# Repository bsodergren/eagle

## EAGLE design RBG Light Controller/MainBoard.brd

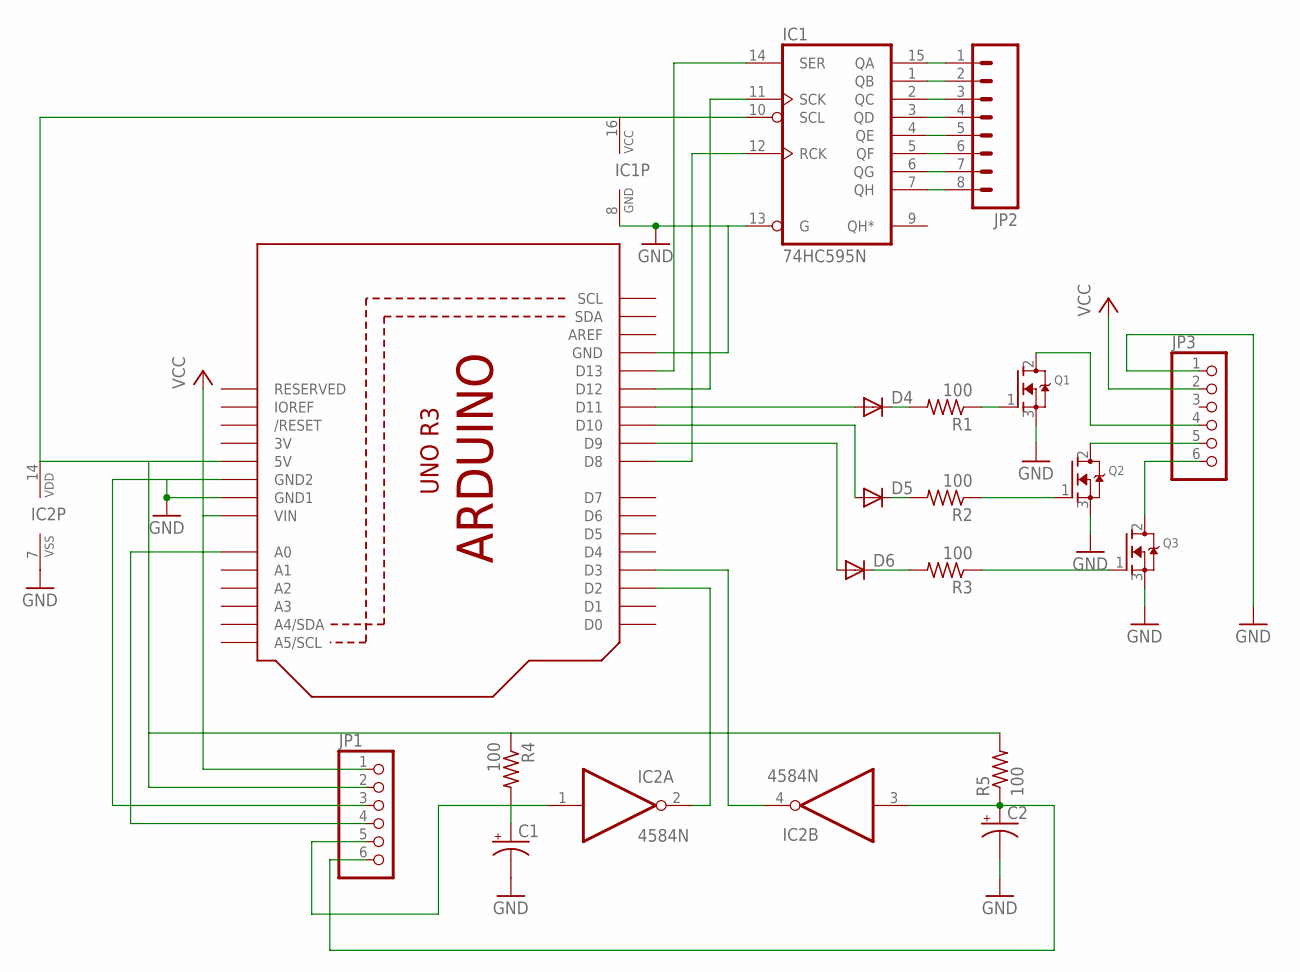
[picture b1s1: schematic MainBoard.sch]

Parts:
C1, C2: CPOL-USE2.5-5; E2,5-5
D4, D5, D6: 1N4148DO35-7; DO35-7
IC1: 74HC595N; DIL16
IC2: 4584N; DIL14
JP1, JP3: PINHD-1X6LOCK; 1X06-BIGLOCK
JP2: M08LOCK; 1X08_LOCK
Q1, Q2, Q3: MOSFET-NGDS_TO220V; TO220V
R1, R2, R3, R4, R5: 100; 0207/10
U1: ARDUINOR3-BPLACE

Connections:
3V: U1.3V
5V: IC1.10 (SCL), IC1.16 (VCC), IC2.14 (VDD), JP1.2, R4.1, R5.2, U1.5V
12V: JP1.1, JP3.2, U1.VIN
BLUE: JP3.6, Q3.2 (D)
GND: C1.-, C2.-, IC1.8 (GND), IC1.13 (G), IC2.7 (VSS), JP1.3, JP3.1, Q1.3 (S), Q2.3 (S), Q3.3 (S), U1.GND, U1.GND1, U1.GND2
GREEN: JP3.4, Q1.2 (D)
unnamed: D6.A, U1.D9
unnamed: D5.A, U1.D10
unnamed: D4.C, R1.2
unnamed: IC2.4 (O), U1.D3
unnamed: IC2.2 (O), U1.D2
unnamed: D5.C, R2.2
unnamed: D6.C, R3.2
unnamed: D4.A, U1.D11
unnamed: IC1.1 (QB), JP2.2
unnamed: IC1.2 (QC), JP2.3
unnamed: IC1.3 (QD), JP2.4
unnamed: IC1.4 (QE), JP2.5
unnamed: IC1.5 (QF), JP2.6
unnamed: IC1.6 (QG), JP2.7
unnamed: IC1.7 (QH), JP2.8
unnamed: IC1.15 (QA), JP2.1
unnamed: IC1.12 (RCK), U1.D8
unnamed: IC1.11 (SCK), U1.D12
unnamed: IC1.14 (SER), U1.D13
unnamed: Q3.1 (G), R3.1
unnamed: Q2.1 (G), R2.1
unnamed: Q1.1 (G), R1.1
RED: JP3.5, Q2.2 (D)
SPEED: JP1.4, U1.A0
SWITCH1: C1.+, IC2.1 (I), JP1.5, R4.2
SWITCH2: C2.+, IC2.3 (I), JP1.6, R5.1

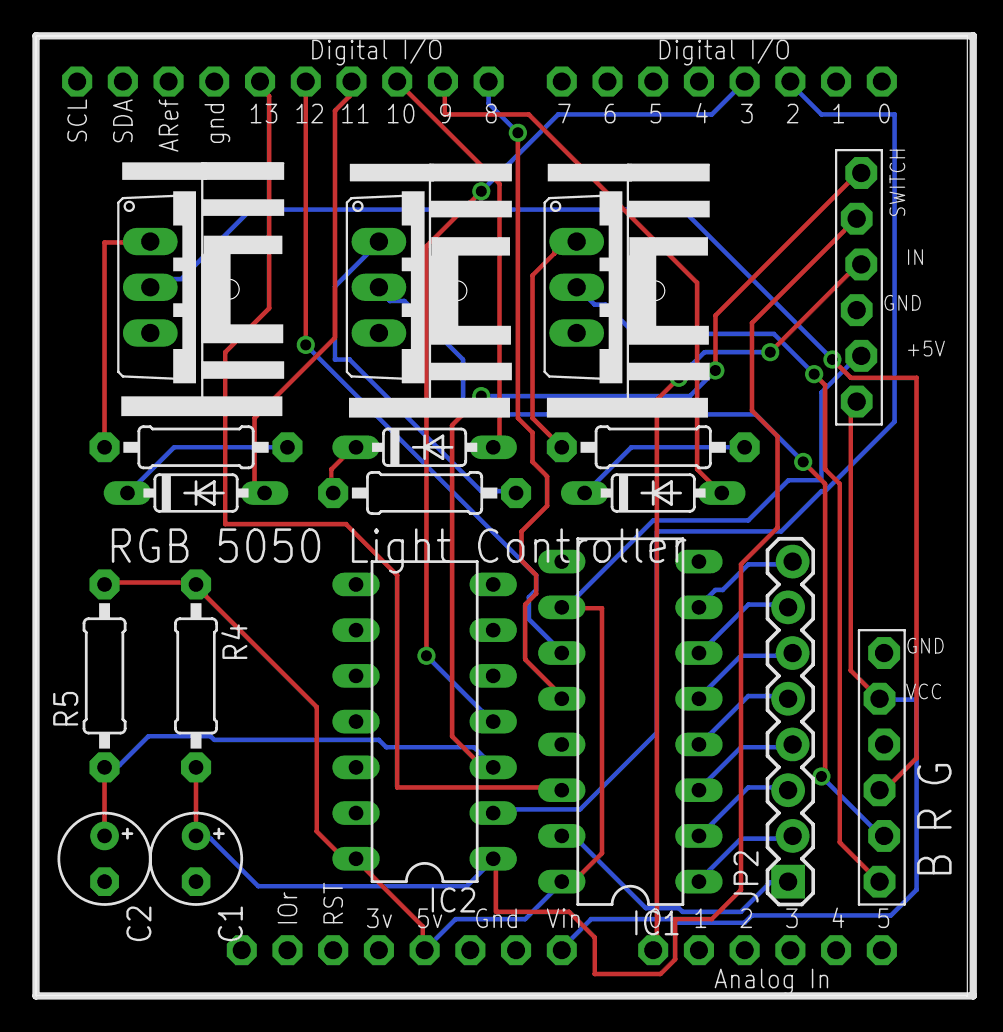
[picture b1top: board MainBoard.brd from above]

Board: 2 copper layers, 51.7 x 53.3 mm, 22 parts (0 on the bottom side), 31 nets.

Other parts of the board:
U$1, U$2, U$3: HEATSINK

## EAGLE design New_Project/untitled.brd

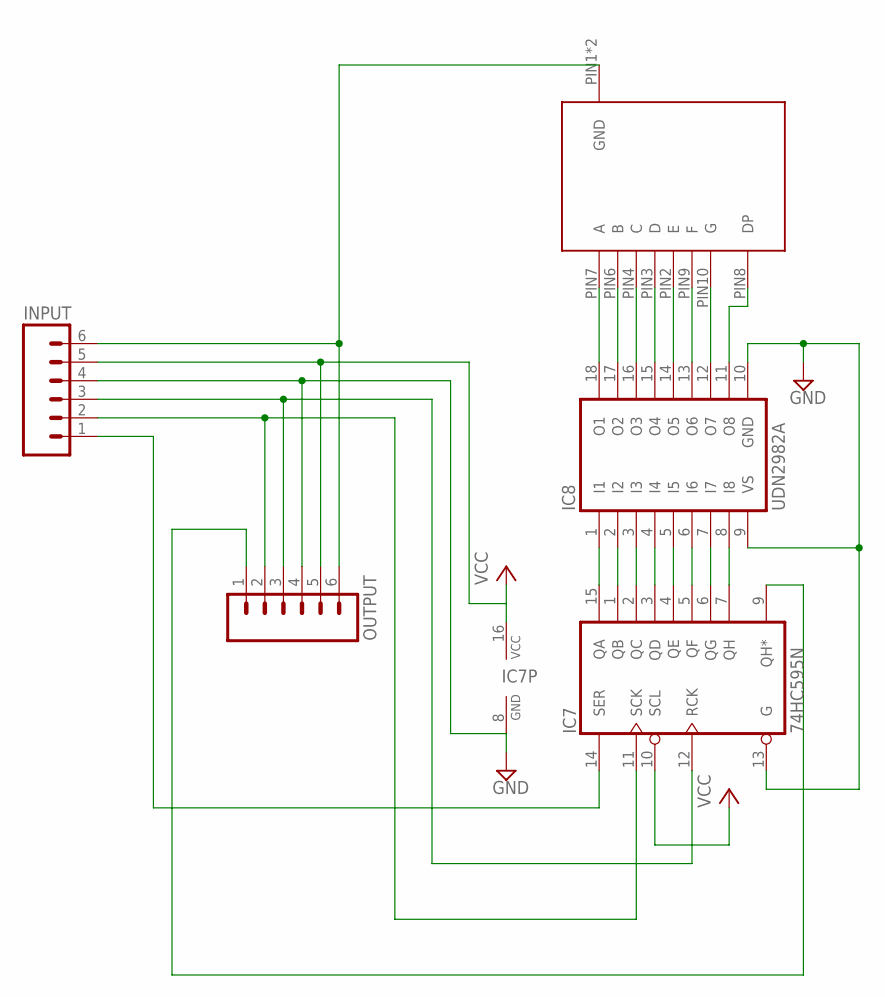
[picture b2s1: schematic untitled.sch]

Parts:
IC7: 74HC595N; DIL16
IC8: UDN2982A; DIL18
INPUT: M06LOCK; 1X06_LOCK
OUTPUT: M06LOCK; 1X06_LOCK
U$1: LSD2325; 10PIN

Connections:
5: IC7.16 (VCC), INPUT.5, OUTPUT.5
GND: IC7.8 (GND), IC7.13 (G), IC8.9 (VS), IC8.10 (GND), INPUT.4, OUTPUT.4
unnamed: IC7.14 (SER), INPUT.1
unnamed: IC7.9 (QH*), OUTPUT.1
unnamed: IC7.11 (SCK), INPUT.2, OUTPUT.2
unnamed: IC7.12 (RCK), INPUT.3, OUTPUT.3
unnamed: INPUT.6, OUTPUT.6, U$1.PIN1 (GND), U$1.PIN5 (GND)
unnamed: IC7.15 (QA), IC8.1 (I1)
unnamed: IC7.1 (QB), IC8.2 (I2)
unnamed: IC7.2 (QC), IC8.3 (I3)
unnamed: IC7.3 (QD), IC8.4 (I4)
unnamed: IC7.4 (QE), IC8.5 (I5)
unnamed: IC7.5 (QF), IC8.6 (I6)
unnamed: IC7.6 (QG), IC8.7 (I7)
unnamed: IC7.7 (QH), IC8.8 (I8)
unnamed: IC8.12 (O7), U$1.PIN10 (G)
unnamed: IC8.13 (O6), U$1.PIN9 (F)
unnamed: IC8.14 (O5), U$1.PIN2 (E)
unnamed: IC8.11 (O8), U$1.PIN8 (DP)
unnamed: IC8.15 (O4), U$1.PIN3 (D)
unnamed: IC8.18 (O1), U$1.PIN7 (A)
unnamed: IC8.16 (O3), U$1.PIN4 (C)
unnamed: IC8.17 (O2), U$1.PIN6 (B)
VCC: IC7.10 (SCL)

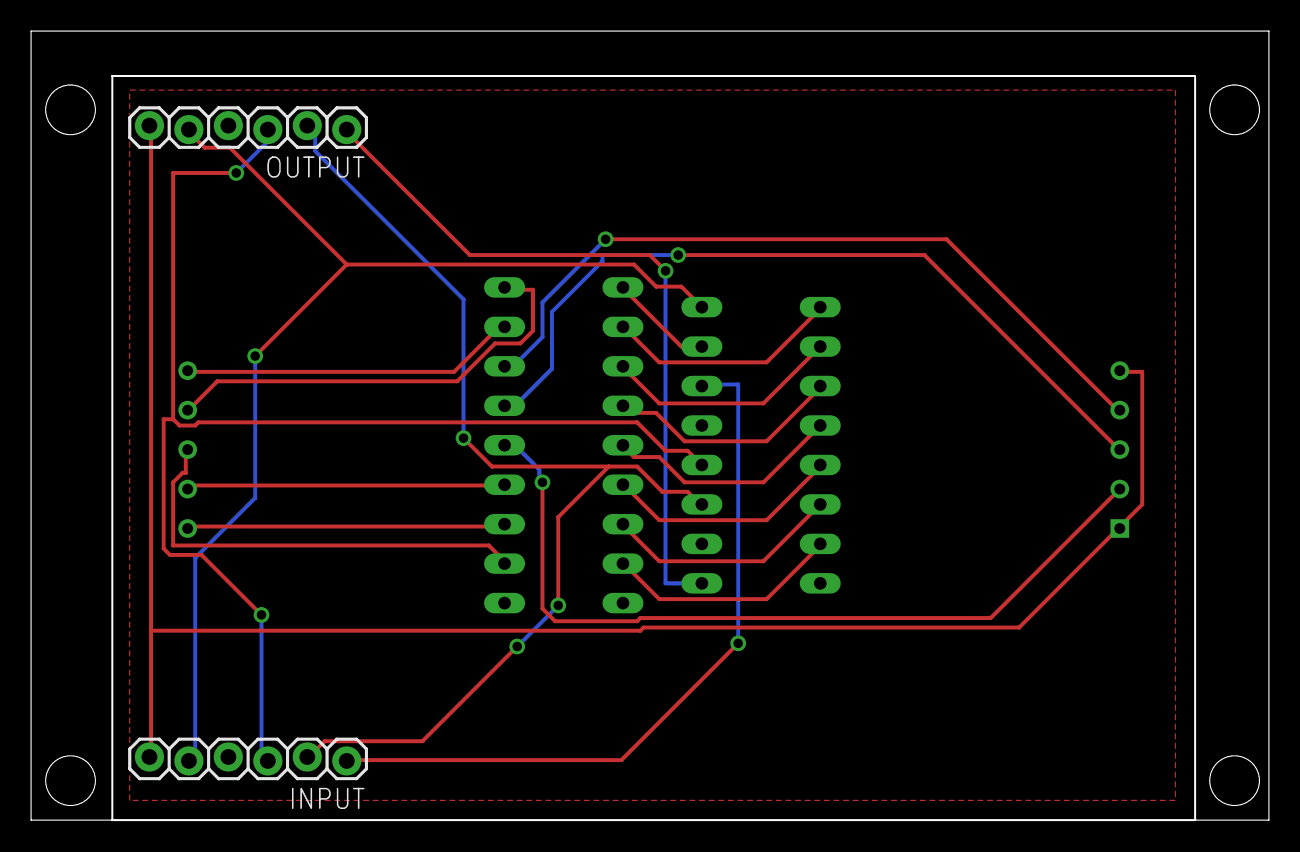
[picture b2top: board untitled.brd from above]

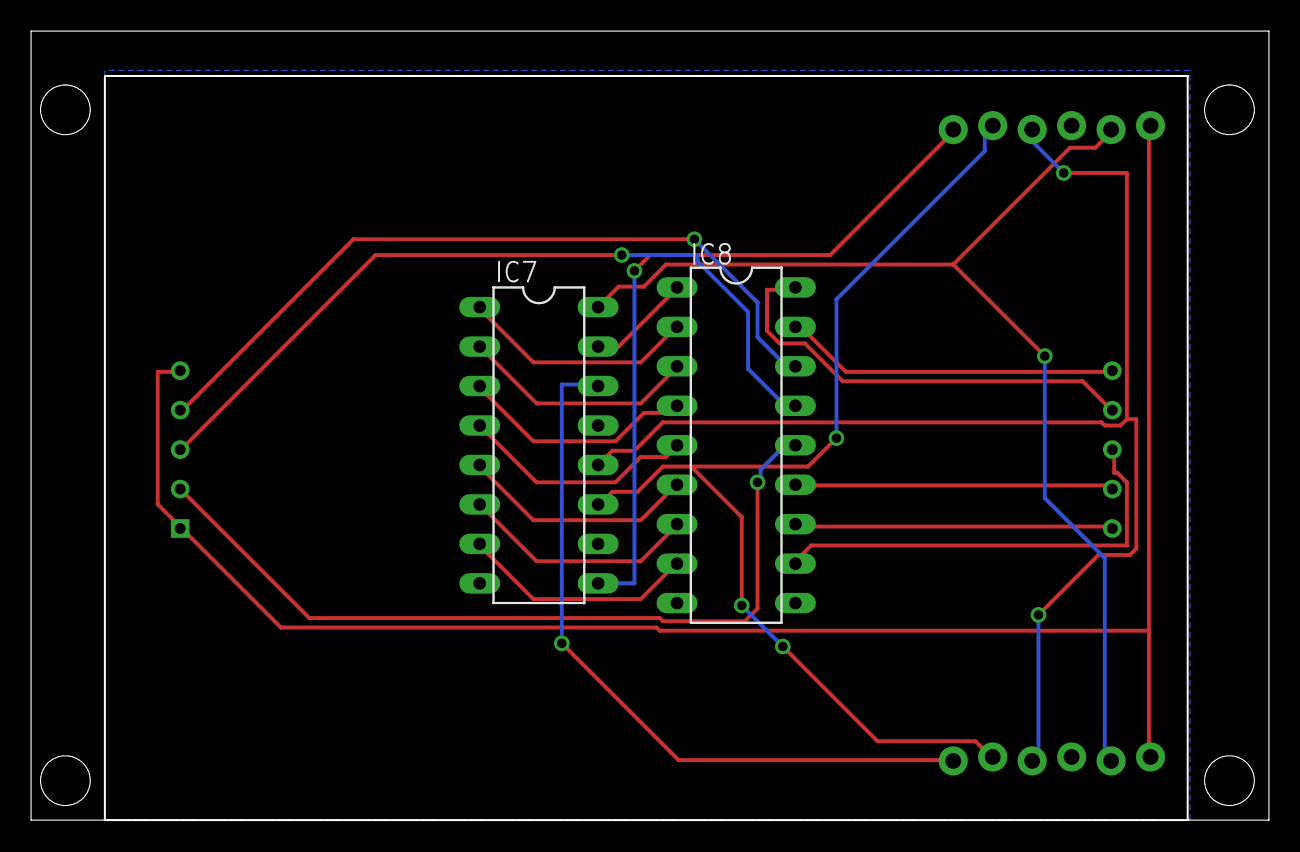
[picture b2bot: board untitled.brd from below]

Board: 2 copper layers, 79.7 x 50.8 mm, 5 parts (2 on the bottom side), 23 nets.

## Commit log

2012-10-09 Added Library & cam job
2012-10-09 updated schematic

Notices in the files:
parts and their libraries:
SparkFun: Licensing: CC v3.0 Share-Alike You are welcome to use this library for commercial purposes.
